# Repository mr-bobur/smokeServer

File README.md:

# 🏢 Smart Building Wireless Smoke & Security Ecosystem (Digital Twin)

Enterprise 9-Story Residential & Commercial Wireless Smoke, CO, Thermal & Perimeter Security Monitoring System with 2D Topological Digital Twin, RS485 Trunk Diagnostics, SIM7670 4G LTE Backhaul, and Automated 60-Second 112 State Emergency Dispatch.

---

## 📐 System Architecture

1. **ESP32-C3 Modular Sensor Endpoints (`firmware/esp32c3_endpoint/`)**
   - Sensors: `SMOKE_MQ2`, `CO_MQ7`, `TEMP_DS18B20`, `DOOR_REED`, `GLASS_BREAK`, `MULTI_FIRE`.
   - **BLE 5.0 Commissioning:** 5–10s long-press on `GPIO 9` broadcasts `[0xFF, 0xFF, CHIP_ID, CAPABILITY_MASK, BATTERY_PCT]`, stores config in NVS, and flashes green status LED 3 times.
   - **Dynamic Beaconing FSM:** 600s deep-sleep standby vs. immediate 1000ms alarm burst + `GPIO 4` piezo siren latch when Smoke > 400 PPM or Temp > 60°C.
2. **ESP32-C3 Floor Sub-Hubs (`firmware/esp32c3_floor_hub/`)**
   - 4x DIP Switch binary floor addressing (`0001` = Floor 1 to `1001` = Floor 9) on `GPIO 1, 2, 3, 4`.
   - RS485 Half-Duplex (`MAX485` on `GPIO 5/6/7`) industrial bus framing with CRC-16 validation: `[0xAA, SRC_FLOOR, MSG_TYPE, LEN, PAYLOAD..., CRC16_H, CRC16_L, 0x55]`.
3. **Central Building Gateway (`firmware/esp32s3_central_gateway/`)**
   - `SIM7670` 4G LTE Cat 1 (`115200` baud AT command pipeline) with MQTT over TLS (`smartbuilding/floor_{floorId}/hub_{hubId}/sensor_{chipId}/telemetry` & `/alarm`).
   - Hardware emergency fallback via `AT+CMGS` (SMS) and `ATD+998...;` (automated voice call).
4. **Core Server (`server/`)**
   - Node.js, Express, TypeScript, Socket.io, MQTT.js, Passport Google OAuth 2.0 (`passport-google-oauth20`), JWT RBAC (`super_admin`, `tenant`, `user`), PM2 Cluster (`ecosystem.config.js`), and MySQL 8.0+ with 1-year `RANGE (UNIX_TIMESTAMP(recorded_at))` partitioning (`server/src/models/ddl.sql`).
5. **Digital Twin Frontend (`client/`)**
   - Next.js 14 App Router, Tailwind CSS, Recharts 1-Year Dual-Axis Analytics (`TelemetryChart.tsx`), Interactive 2D Floor Plan (`BlueprintViewer.tsx`, `SensorPin.tsx`, `SensorModal.tsx`), and 3 Role Portals (`/admin`, `/tenant`, `/resident`).

---

## 🚀 Quick Start

### 1. Start the Core Backend Server (Port 5000)
```bash
cd server
npm run dev
```

### 2. Start the Next.js Digital Twin Frontend (Port 3000)
```bash
cd client
npm run dev
```

Open **http://localhost:3000** in your browser:
- **Super Admin Console:** `http://localhost:3000/admin`
- **Shirkat (Building Manager) Dashboard:** `http://localhost:3000/tenant`
- **Resident User Portal (Floor 4, Apt 42):** `http://localhost:3000/resident`
- **Google OAuth 2.0 / Role Switcher Login:** `http://localhost:3000/login`

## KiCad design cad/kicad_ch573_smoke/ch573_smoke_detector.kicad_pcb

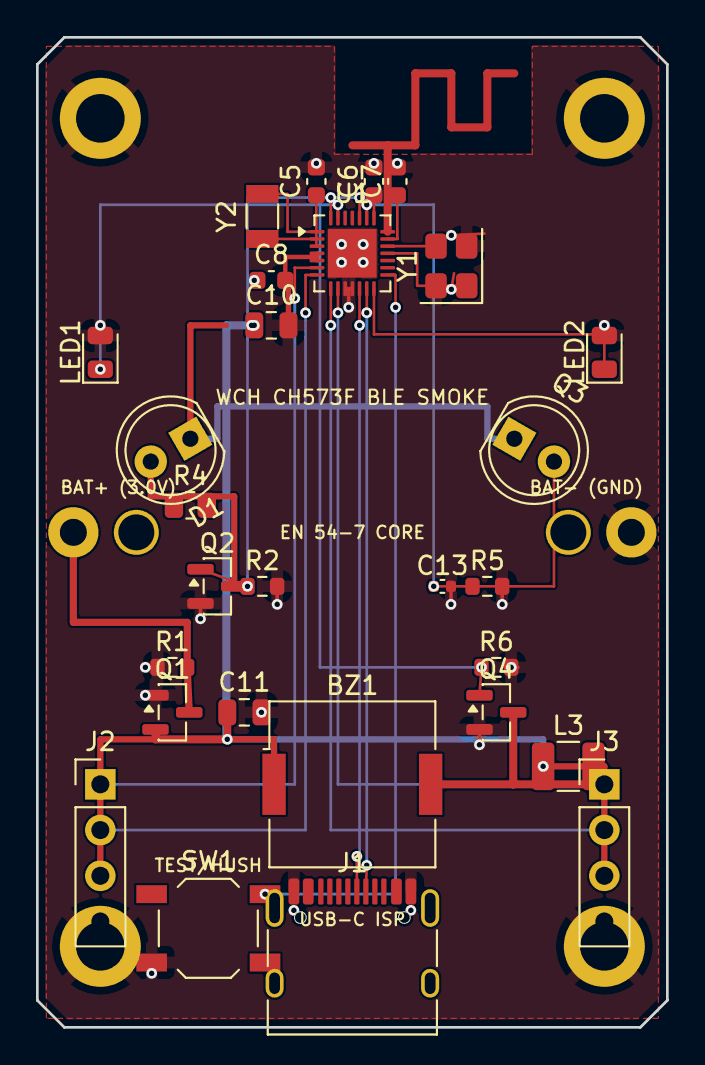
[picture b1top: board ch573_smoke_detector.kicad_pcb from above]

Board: 2 copper layers, 35.0 x 55.0 mm, 28 parts (0 on the bottom side), 25 nets.

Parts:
BZ1: Buzzer_Murata_PKMCS0909E
C5, C6, C7, C8: C_0603_1608Metric
C10, C11: C_0805_2012Metric
C13: C_0402_1005Metric
D1: LED_D5.0mm
J1: USB_C_Receptacle_HRO_TYPE-C-31-M-12
J2, J3: PinHeader_1x04_P2.54mm_Vertical
L3: L_1210_3225Metric
LED1, LED2: LED_0805_2012Metric
Q1, Q2, Q4: SOT-23
Q3: LED_D5.0mm
R1, R2, R5, R6: R_0603_1608Metric
R4: R_0805_2012Metric
SW1: SW_SPST_TL3342
U1: WQFN-28-1EP_4x4mm_P0.4mm_EP2.7x2.7mm
Y1: Crystal_SMD_3225-4Pin_3.2x2.5mm
Y2: Crystal_SMD_3215-2Pin_3.2x1.5mm

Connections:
BUZZER_DRAIN: BZ1.2, L3.2, Q4.3
GND: C5.2, C6.2, C7.2, C8.2, C10.2, C11.2, C13.2, J1.A1, J1.A12, J1.B1, J1.B12, J2.4, J3.4, LED1.2, LED2.2, Q1.1, Q2.2, Q4.2, R1.1, R2.2, R5.2, R6.2, SW1.2, U1.10, U1.11, U1.29, Y1.2, Y1.4
IR_LED_CATHODE: D1.2, Q2.3
PA3_LED: LED1.1, U1.27
PA4_AIN0: C13.1, Q3.2, R5.1, U1.23
PA5_IR_PULSE: Q2.1, R2.1, U1.24
PA8_TX: J2.1, U1.6
PA9_RX: J2.2, U1.7
PA12_BUZZER: Q4.1, R6.1, U1.28
PB4_TEST: SW1.1, U1.15
PB7_ALARM_LED: LED2.1, U1.14
PB10_USB_DP: J1.A6, J1.B6, U1.13
PB11_USB_DM: J1.A7, J1.B7, U1.12
PB14_SWDIO: J3.1, U1.9
PB15_SWCLK: J3.2, U1.8
VBAT: Q1.3, R1.2
VBUS: J1.A4, J1.A9, J1.B4, J1.B9
VDCIA: C6.1, U1.22
VDCID: C5.1, U1.3
VDD: BZ1.1, C8.1, C10.1, C11.1, D1.1, J2.3, J3.3, L3.1, Q1.2, Q3.1, R4.1, R4.2, U1.4, U1.5
VINTA: C7.1, U1.20
X32KI: U1.2, Y2.2
X32KO: U1.1, Y2.1
X32MI: U1.19, Y1.3
X32MO: U1.18, Y1.1

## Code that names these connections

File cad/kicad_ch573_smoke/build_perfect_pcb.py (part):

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
net_names = [
    "GND", "VBAT", "VDD", "VDCID", "VDCIA", "VINTA",
    "RF_ANT", "PA4_AIN0", "PA5_IR_PULSE", "PA12_BUZZER",
    "PA8_TX", "PA9_RX", "PB14_SWDIO", "PB15_SWCLK",
    "PB10_USB_DP", "PB11_USB_DM", "PB4_TEST", "PB22_BOOT", "PB23_RST",
    "PA3_LED", "PB7_ALARM_LED", "I2C_SCL", "I2C_SDA",
    "BUZZER_DRAIN", "IR_LED_CATHODE", "VBUS",
    "X32MO", "X32MI", "X32KO", "X32KI"
]
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# U1: WCH CH573F QFN-28 (at 0.0, -15.5)
ch573_map = {
    "1": "X32KO", "2": "X32KI", "3": "VDCID", "4": "VDD", "5": "VDD",
    "6": "PA8_TX", "7": "PA9_RX", "8": "PB15_SWCLK", "9": "PB14_SWDIO",
    "10": "GND", "11": "GND", "12": "PB11_USB_DM", "13": "PB10_USB_DP",
    "14": "PB7_ALARM_LED", "15": "PB4_TEST", "16": "PB23_RST", "17": "PB22_BOOT",
    "18": "X32MO", "19": "X32MI", "20": "VINTA", "21": "RF_ANT",
    "22": "VDCIA", "23": "PA4_AIN0", "24": "PA5_IR_PULSE",
    "25": "I2C_SCL", "26": "I2C_SDA", "27": "PA3_LED", "28": "PA12_BUZZER",
    "29": "GND"
}
u1 = load_fp("Package_DFN_QFN.pretty", "WQFN-28-1EP_4x4mm_P0.4mm_EP2.7x2.7mm", "U1", 0.0, -15.5, net_map=ch573_map)
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})

# Decoupling Caps (placed immediately adjacent to their respective pins)
# C5 (2.2uF VDCID, Pin 3) at (-2.0, -19.5), angle 90
c5 = load_fp("Capacitor_SMD.pretty", "C_0603_1608Metric", "C5", -2.0, -19.5, angle=90, net_map={"1": "VDCID", "2": "GND"})
# C6 (1.0uF VDCIA, Pin 22) at (1.2, -19.5), angle 90
c6 = load_fp("Capacitor_SMD.pretty", "C_0603_1608Metric", "C6", 1.2, -19.5, angle=90, net_map={"1": "VDCIA", "2": "GND"})
# C7 (1.0uF VINTA, Pin 20) at (2.5, -19.5), angle 90
c7 = load_fp("Capacitor_SMD.pretty", "C_0603_1608Metric", "C7", 2.5, -19.5, angle=90, net_map={"1": "VINTA", "2": "GND"})
# C8 (0.1uF VDD, Pins 4/5) at (-4.5, -14.0), angle 0
c8 = load_fp("Capacitor_SMD.pretty", "C_0603_1608Metric", "C8", -4.5, -14.0, angle=0, net_map={"1": "VDD", "2": "GND"})
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
# Optical Smoke Sensing Circuit
d1 = load_fp("LED_THT.pretty", "LED_D5.0mm", "D1", -9.0, -5.2, angle=210, net_map={"1": "VDD", "2": "IR_LED_CATHODE"})
q3 = load_fp("LED_THT.pretty", "LED_D5.0mm", "Q3", 9.0, -5.2, angle=330, net_map={"1": "VDD", "2": "PA4_AIN0"})

q2 = load_fp("Package_TO_SOT_SMD.pretty", "SOT-23", "Q2", -7.5, 3.0, net_map={"1": "PA5_IR_PULSE", "2": "GND", "3": "IR_LED_CATHODE"})
r2 = load_fp("Resistor_SMD.pretty", "R_0603_1608Metric", "R2", -5.0, 3.0, net_map={"1": "PA5_IR_PULSE", "2": "GND"})
r4 = load_fp("Resistor_SMD.pretty", "R_0805_2012Metric", "R4", -9.0, -1.5, net_map={"1": "VDD", "2": "VDD"})
r5 = load_fp("Resistor_SMD.pretty", "R_0603_1608Metric", "R5", 7.5, 3.0, net_map={"1": "PA4_AIN0", "2": "GND"})
c13 = load_fp("Capacitor_SMD.pretty", "C_0402_1005Metric", "C13", 5.0, 3.0, net_map={"1": "PA4_AIN0", "2": "GND"})

# Acoustic Siren Circuit
q4 = load_fp("Package_TO_SOT_SMD.pretty", "SOT-23", "Q4", 8.0, 10.0, net_map={"1": "PA12_BUZZER", "2": "GND", "3": "BUZZER_DRAIN"})
r6 = load_fp("Resistor_SMD.pretty", "R_0603_1608Metric", "R6", 8.0, 7.5, net_map={"1": "PA12_BUZZER", "2": "GND"})
l3 = load_fp("Inductor_SMD.pretty", "L_1210_3225Metric", "L3", 12.0, 13.0, net_map={"1": "VDD", "2": "BUZZER_DRAIN"})
bz1 = load_fp("Buzzer_Beeper.pretty", "Buzzer_Murata_PKMCS0909E", "BZ1", 0.0, 14.0, net_map={"1": "VDD", "2": "BUZZER_DRAIN"})

# Indicators & Switch
led1 = load_fp("LED_SMD.pretty", "LED_0805_2012Metric", "LED1", -14.0, -10.0, angle=90, net_map={"1": "PA3_LED", "2": "GND"})
led2 = load_fp("LED_SMD.pretty", "LED_0805_2012Metric", "LED2", 14.0, -10.0, angle=90, net_map={"1": "PB7_ALARM_LED", "2": "GND"})
sw1 = load_fp("Button_Switch_SMD.pretty", "SW_SPST_TL3342", "SW1", -8.0, 22.0, net_map={"1": "PB4_TEST", "2": "GND", "3": "PB4_TEST", "4": "GND"})

# Connectors
j1 = load_fp("Connector_USB.pretty", "USB_C_Receptacle_HRO_TYPE-C-31-M-12", "J1", 0.0, 24.0, angle=0, net_map={
    "A1": "GND", "B12": "GND", "A12": "GND", "B1": "GND",
    "A4": "VBUS", "B9": "VBUS", "A9": "VBUS", "B4": "VBUS",
    "A6": "PB10_USB_DP", "B6": "PB10_USB_DP",
    "A7": "PB11_USB_DM", "B7": "PB11_USB_DM"
})
j2 = load_fp("Connector_PinHeader_2.54mm.pretty", "PinHeader_1x04_P2.54mm_Vertical", "J2", -14.0, 14.0, angle=0, net_map={
    "1": "PA8_TX", "2": "PA9_RX", "3": "VDD", "4": "GND"
})
j3 = load_fp("Connector_PinHeader_2.54mm.pretty", "PinHeader_1x04_P2.54mm_Vertical", "J3", 14.0, 14.0, angle=0, net_map={
    "1": "PB14_SWDIO", "2": "PB15_SWCLK", "3": "VDD", "4": "GND"
})

# -----------------------------------------------------------------------------
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print("Routing high-frequency signals and crystals...")

# --- 32 MHz Crystal (Y1) ---
# Pad 3 (X32MI) at (4.65, -15.9) connects straight to U1 Pin 19 at (1.962, -15.9)
add_track(pcbnew.F_Cu, [(1.962, -15.9), (4.65, -15.9)], width=0.15, net_name="X32MI")
# Pad 1 (X32MO) at (6.35, -13.7) connects to U1 Pin 18 at (1.962, -15.5)
add_track(pcbnew.F_Cu, [(1.962, -15.5), (3.6, -15.5), (3.6, -13.7), (6.35, -13.7)], width=0.15, net_name="X32MO")

# --- 32.768 kHz Crystal (Y2) ---
# Pad 2 (X32KI) at (-5.0, -16.3) connects straight to U1 Pin 2 at (-1.962, -16.3)
add_track(pcbnew.F_Cu, [(-1.962, -16.3), (-5.0, -16.3)], width=0.15, net_name="X32KI")
# Pad 1 (X32KO) at (-5.0, -18.8) connects to U1 Pin 1 at (-1.962, -16.7)
add_track(pcbnew.F_Cu, [(-1.962, -16.7), (-3.6, -16.7), (-3.6, -18.8), (-5.0, -18.8)], width=0.15, net_name="X32KO")

# --- Decoupling Caps Direct Connections ---
# C5 (VDCID, Pin 3): (-1.962, -15.9) to (-2.0, -18.725)
add_track(pcbnew.F_Cu, [(-1.962, -15.9), (-2.0, -15.9), (-2.0, -18.725)], width=0.15, net_name="VDCID")
# C7 (VINTA, Pin 20): (1.962, -16.3) to (2.5, -18.725)
add_track(pcbnew.F_Cu, [(1.962, -16.3), (2.5, -16.3), (2.5, -18.725)], width=0.15, net_name="VINTA")
# C6 (VDCIA, Pin 22): (1.20, -17.462) to (1.20, -18.725)
add_track(pcbnew.F_Cu, [(1.20, -17.462), (1.20, -18.725)], width=0.15, net_name="VDCIA")

# C8 & C10 (VDD, Pins 4/5): Pins 4 & 5 at (-1.962, -15.5) and (-1.962, -15.1)
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
print("Routing conflict-free layer-separated interconnects...")

# --- 1. PA8_TX: U1 Pin 6 (-1.962, -14.70) to J2 Pin 1 (-14.0, 14.0) ---
add_track(pcbnew.F_Cu, [(-1.962, -14.70), (-3.2, -14.70), (-3.2, -13.0)], width=0.15, net_name="PA8_TX")
add_via(-3.2, -13.0, "PA8_TX")
add_track(pcbnew.B_Cu, [(-3.2, -13.0), (-3.2, 14.0), (-14.0, 14.0)], width=0.15, net_name="PA8_TX")

# --- 2. PA9_RX: U1 Pin 7 (-1.962, -14.30) to J2 Pin 2 (-14.0, 16.54) ---
add_track(pcbnew.F_Cu, [(-1.962, -14.30), (-2.6, -14.30), (-2.6, -12.2)], width=0.15, net_name="PA9_RX")
add_via(-2.6, -12.2, "PA9_RX")
add_track(pcbnew.B_Cu, [(-2.6, -12.2), (-2.6, 16.54), (-14.0, 16.54)], width=0.15, net_name="PA9_RX")

# --- 3. PB14_SWDIO: U1 Pin 9 (-0.80, -13.537) to J3 Pin 1 (14.0, 14.0) ---
add_track(pcbnew.F_Cu, [(-0.80, -13.537), (-0.80, -12.2)], width=0.15, net_name="PB14_SWDIO")
add_via(-0.80, -12.2, "PB14_SWDIO")
add_track(pcbnew.B_Cu, [(-0.80, -12.2), (-0.80, 14.0), (14.0, 14.0)], width=0.15, net_name="PB14_SWDIO")

# --- 4. PB15_SWCLK: U1 Pin 8 (-1.20, -13.537) to J3 Pin 2 (14.0, 16.54) ---
add_track(pcbnew.F_Cu, [(-1.20, -13.537), (-1.20, -11.5)], width=0.15, net_name="PB15_SWCLK")
add_via(-1.20, -11.5, "PB15_SWCLK")
add_track(pcbnew.B_Cu, [(-1.20, -11.5), (-1.20, 16.54), (14.0, 16.54)], width=0.15, net_name="PB15_SWCLK")

# --- 5. PB10_USB_DP: U1 Pin 13 (0.80, -13.537) to J1 Pad B6 (0.75, 19.955) ---
add_track(pcbnew.F_Cu, [(0.80, -13.537), (0.80, -12.2)], width=0.15, net_name="PB10_USB_DP")
add_via(0.80, -12.2, "PB10_USB_DP")
add_track(pcbnew.B_Cu, [(0.80, -12.2), (0.80, 18.5)], width=0.15, net_name="PB10_USB_DP")
add_via(0.80, 18.5, "PB10_USB_DP")
add_track(pcbnew.F_Cu, [(0.80, 18.5), (0.75, 19.955)], width=0.15, net_name="PB10_USB_DP")

# --- 6. PB11_USB_DM: U1 Pin 12 (0.40, -13.537) to J1 Pad A7 (0.25, 19.955) ---
add_track(pcbnew.F_Cu, [(0.40, -13.537), (0.40, -11.5)], width=0.15, net_name="PB11_USB_DM")
add_via(0.40, -11.5, "PB11_USB_DM")
add_track(pcbnew.B_Cu, [(0.40, -11.5), (0.40, 18.0), (0.25, 18.0)], width=0.15, net_name="PB11_USB_DM")
add_via(0.25, 18.0, "PB11_USB_DM")
add_track(pcbnew.F_Cu, [(0.25, 18.0), (0.25, 19.955)], width=0.15, net_name="PB11_USB_DM")

# --- 7. PB7_ALARM_LED: U1 Pin 14 (1.20, -13.537) to LED2 Pad 1 (14.0, -9.062) ---
add_track(pcbnew.F_Cu, [(1.20, -13.537), (1.20, -11.0), (14.0, -11.0), (14.0, -9.062)], width=0.15, net_name="PB7_ALARM_LED")

# --- 8. PA3_LED: U1 Pin 27 (-0.80, -17.462) to LED1 Pad 1 (-14.0, -9.062) ---
add_track(pcbnew.F_Cu, [(-0.80, -17.462), (-0.80, -18.2)], width=0.15, net_name="PA3_LED")
add_via(-0.80, -18.2, "PA3_LED")
add_track(pcbnew.B_Cu, [(-0.80, -18.2), (-14.0, -18.2), (-14.0, -9.062)], width=0.15, net_name="PA3_LED")
add_via(-14.0, -9.062, "PA3_LED")

# --- 9. PB4_TEST: U1 Pin 15 (1.962, -14.30) to SW1 Pad 1 (-4.85, 20.10) ---
add_track(pcbnew.F_Cu, [(1.962, -14.30), (2.4, -14.30), (2.4, -12.5)], width=0.15, net_name="PB4_TEST")
add_via(2.4, -12.5, "PB4_TEST")
add_track(pcbnew.B_Cu, [(2.4, -12.5), (2.4, 20.10), (-4.85, 20.10)], width=0.15, net_name="PB4_TEST")
add_via(-4.85, 20.10, "PB4_TEST")

# --- 10. PA12_BUZZER: U1 Pin 28 (-1.20, -17.462) to Q4 Pad 1 (7.062, 9.05) & R6 Pad 1 (7.175, 7.50) ---
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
